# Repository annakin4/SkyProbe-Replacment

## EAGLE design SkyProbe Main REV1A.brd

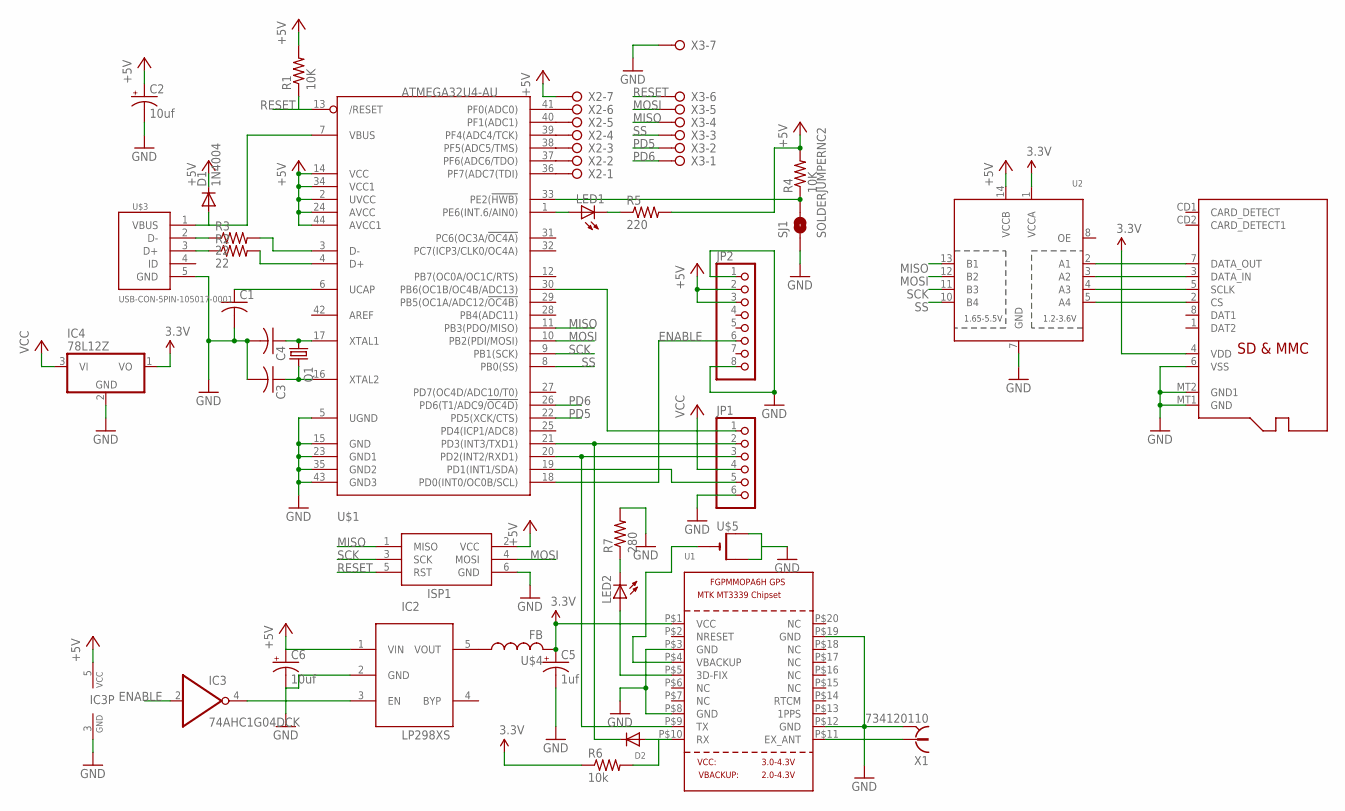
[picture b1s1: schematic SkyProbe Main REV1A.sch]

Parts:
C1, C3, C4: C-USC0805; C0805
C2: 10uf; 140CLH-0810
C5: 1uf; VISHAY_C
C6: 10uf; VISHAY_C
D1: 1N4004; DO41-10
D2: DIODESOT23_WAVE; SOT23-W
IC2: LP298XS; SOT23-5L
IC3: 74AHC1G04DCK; SC70-5
IC4: 78L12Z; TO92
ISP1: AVRISP-6; AVRISP
JP1: PINHD-1X6; 1X06
JP2: PINHD-1X8CLEANBIG; 1X08-CLEANBIG
LED1: LEDB155; Q62902-B155
LED2: LEDCHIPLED_0603; CHIPLED_0603
Q1: CRYSTALCTS406; CTS406
R1, R4: 10K; R0805
R2, R3: 22; R0805
R5: 220; R0805
R6: 10k; M0805
R7: 280; M0805
SJ1: SOLDERJUMPERNC2; SJ_2S-NOTRACE
U1: GPS_FGPMMOPA6H; FGPMMOPA6H
U2: TXB0104PWR; TSSOP14
U$1: ATMEGA32U4-AU; TQFP44
U$3: USB-CON-5PIN-105017-0001; USB-MICRO-MOLEX-105017-0001
U$4: FB
U$5: CR1220SMT; CR1220-SMD
U$6: MICROSD
X1: 734120110
X2, X3: W237-07P; W237-7P

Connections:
3.3V: C5.+, IC4.1 (VO), R6.1, U1.P$1 (VCC), U2.1 (VCCA), U$4.P$2 (2)
+5V: C2.+, C6.+, D1.C, IC2.1 (VIN), IC3.5 (VCC), ISP1.2 (VCC), JP2.2, JP2.3, R1.2, R4.2, R5.2, U2.14 (VCCB), U$1.2 (UVCC), U$1.14 (VCC), U$1.24 (AVCC), U$1.34 (VCC1), U$1.44 (AVCC1), X2.7
ENABLE: IC3.2 (I), JP2.6, U$1.18 (PD0(INT0/OC0B/SCL))
GND: C1.2, C2.-, C3.2, C4.2, C5.-, C6.-, IC2.2 (GND), IC3.3 (GND), IC4.2 (GND), ISP1.6 (GND), JP1.6, JP2.1, JP2.8, R7.2, SJ1.1, U1.P$3 (GND), U1.P$8 (GND), U1.P$12 (GND), U1.P$19 (GND), U2.7 (GND), U$1.5 (UGND), U$1.15 (GND), U$1.23 (GND1), U$1.35 (GND2), U$1.43 (GND3), U$3.5 (GND), U$5.+$1 (+), U$5.+$2 (+1), U$6.6 (VSS), U$6.MT1 (GND), U$6.MT2 (GND1), X1.S@1 (2), X1.S@2 (2), X1.S@3 (2), X3.7
MISO: ISP1.1 (MISO), U2.13 (B1), U$1.11 (PB3(PDO/MISO)), X3.4
MOSI: ISP1.4 (MOSI), U2.12 (B2), U$1.10 (PB2(PDI/MOSI)), X3.5
unnamed: C1.1, U$1.6 (UCAP)
unnamed: R2.1, U$3.3 (D+)
unnamed: R3.2, U$1.3 (D-)
unnamed: C4.1, Q1.1, U$1.17 (XTAL1)
unnamed: C3.1, Q1.3 (2), U$1.16 (XTAL2)
unnamed: R2.2, U$1.4 (D+)
unnamed: R3.1, U$3.2 (D-)
unnamed: D1.A, U$1.7 (VBUS), U$3.1 (VBUS)
unnamed: D2.3 (C), JP1.2, U$1.21 (PD3(INT3/TXD1))
unnamed: JP1.3, U1.P$9 (TX), U$1.20 (PD2(INT2/RXD1))
unnamed: R4.1, SJ1.2, U$1.33 (PE2(!HWB))
unnamed: JP1.5, U$1.19 (PD1(INT1/SDA))
unnamed: JP1.1, U$1.30 (PB6(OC1B/OC4B/ADC13))
unnamed: LED1.A, U$1.1 (PE6(INT.6/AIN0))
unnamed: LED1.K (C), R5.1
unnamed: D2.1 (A), R6.2, U1.P$10 (RX)
unnamed: U$1.41 (PF0(ADC0)), X2.6
unnamed: U$1.40 (PF1(ADC1)), X2.5
unnamed: U$1.39 (PF4(ADC4/TCK)), X2.4
unnamed: U$1.38 (PF5(ADC5/TMS)), X2.3
unnamed: U$1.37 (PF6(ADC6/TDO)), X2.2
unnamed: U$1.36 (PF7(ADC7(TDI)), X2.1
unnamed: U1.P$4 (VBACKUP), U$5.-
unnamed: IC2.5 (VOUT), U$4.P$1 (1)
unnamed: U1.P$11 (EX_ANT), X1.1
unnamed: LED2.A, U1.P$5 (3D-FIX)
unnamed: LED2.C, R7.1
unnamed: IC2.3 (EN), IC3.4 (O)
unnamed: U2.2 (A1), U$6.7 (DATA_OUT)
unnamed: U2.3 (A2), U$6.3 (DATA_IN)
unnamed: U2.4 (A3), U$6.5 (SCLK)
unnamed: U2.5 (A4), U$6.2 (CS)
PD5: U$1.22 (PD5(XCK/CTS)), X3.2
PD6: U$1.26 (PD6(T1/ADC9/!OC4D)), X3.1
RESET: ISP1.5 (RST), R1.1, U$1.13 (/RESET), X3.6
SCK: ISP1.3 (SCK), U2.11 (B3), U$1.9 (PB1(SCK))
SS: U2.10 (B4), U$1.8 (PB0(SS)), X3.3
VCC: IC4.3 (VI), JP1.4
VDD: U$6.4 (VDD)

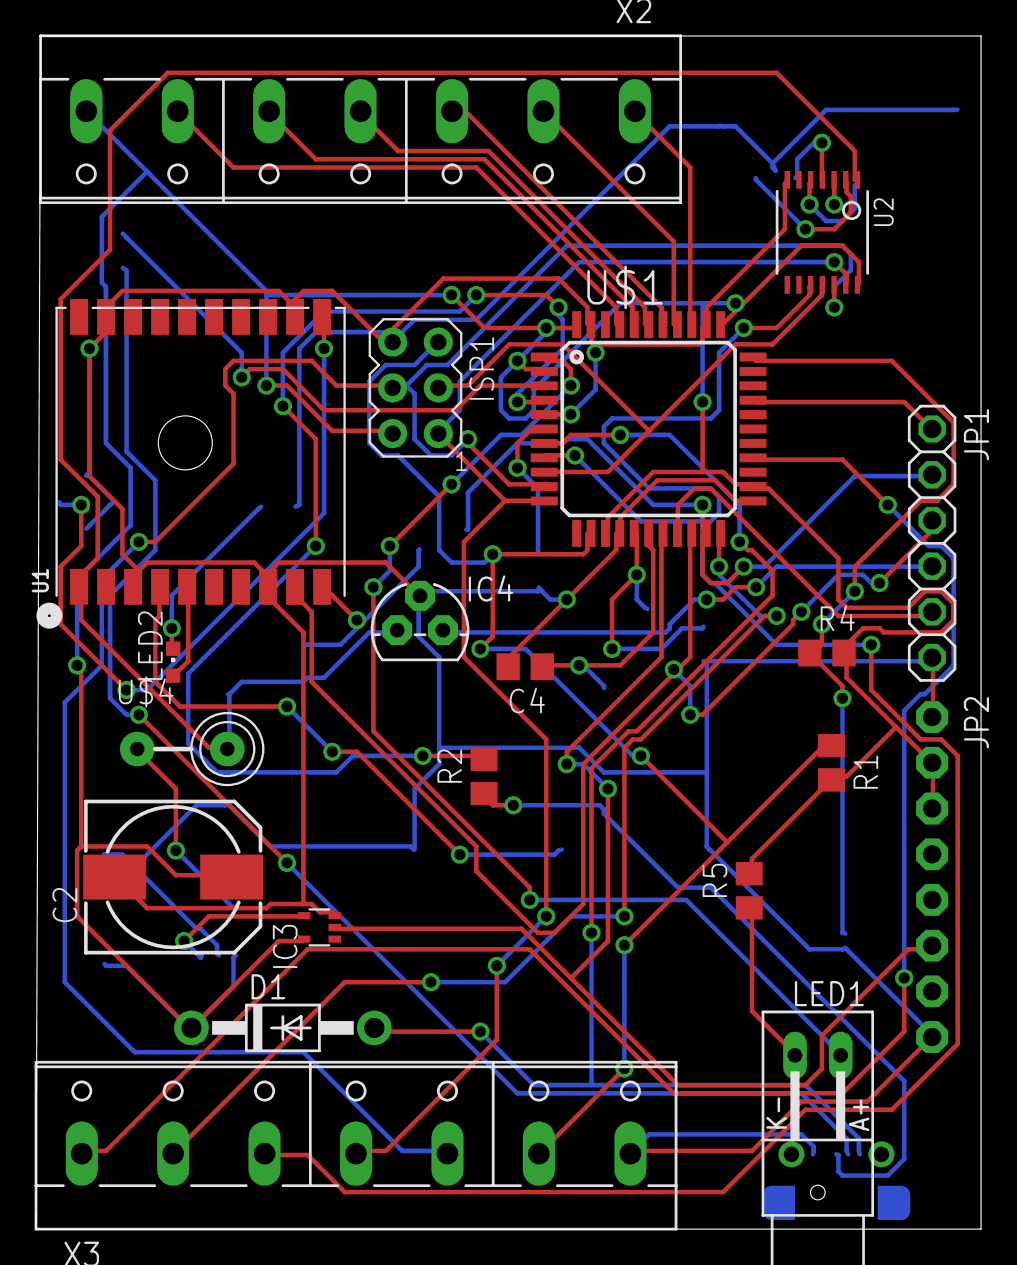
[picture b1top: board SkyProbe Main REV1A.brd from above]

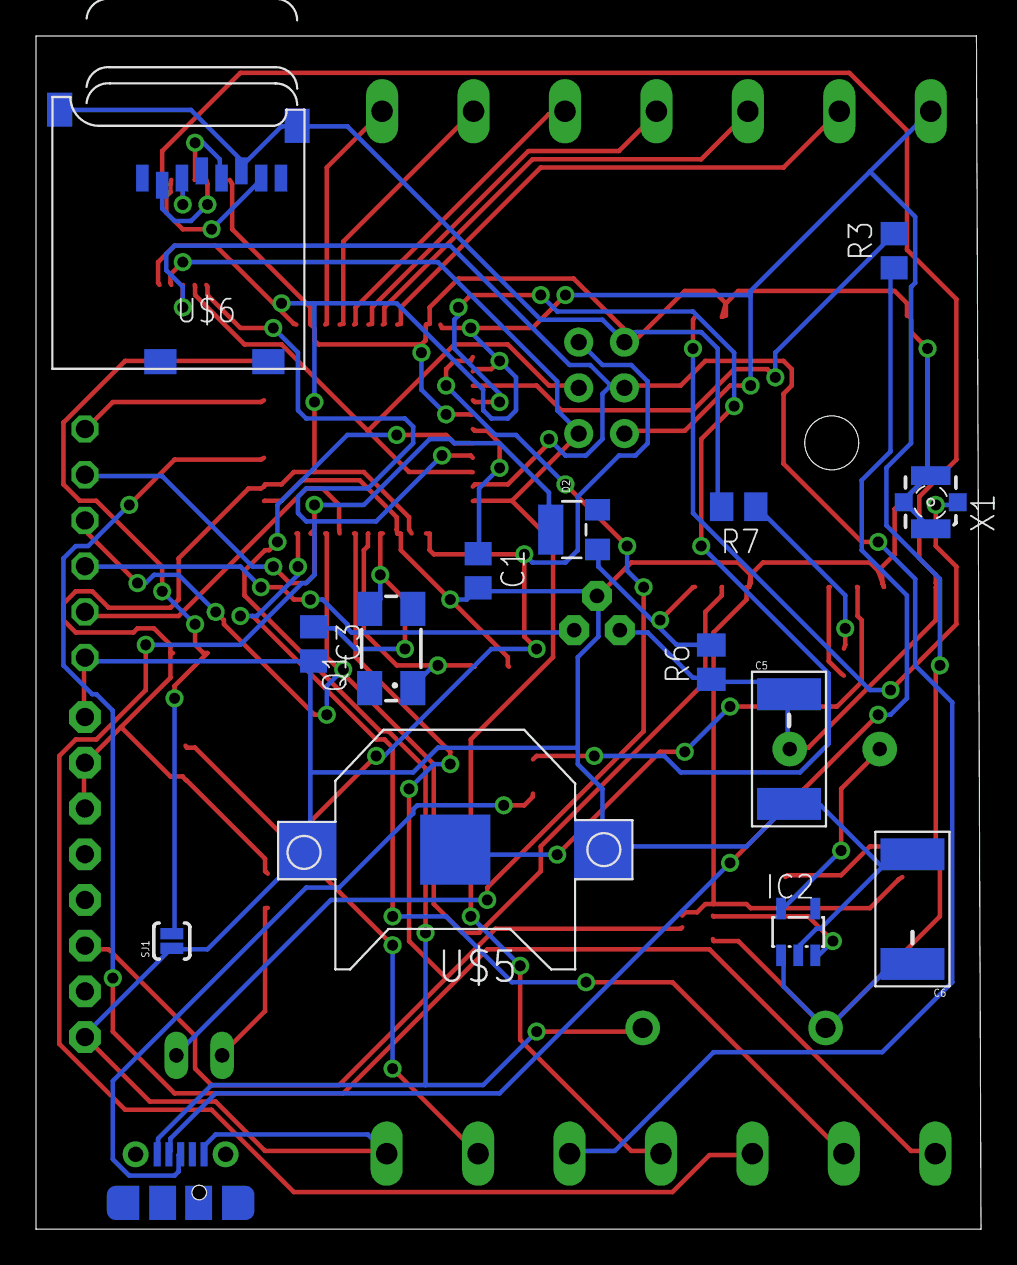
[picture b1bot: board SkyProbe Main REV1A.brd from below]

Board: 2 copper layers, 52.5 x 66.3 mm, 35 parts (15 on the bottom side), 44 nets.

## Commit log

2016-07-11 :octocat: Added .gitattributes & .gitignore files
2016-07-11 First Upload

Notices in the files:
parts and their libraries:
SparkFun-Retired: Licensing:Creative Commons ShareAlike 4.0 International - https://creativecommons.org/licenses/by-sa/4.0
